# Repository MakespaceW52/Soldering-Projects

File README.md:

# Soldering Projects

\
Photo: © TINCON

Einfache Lötprojekte für den Einsatz in Bildungseinrichtungen und Makespaces.
Für alle Projekte stellen wir Gerber-Dateien zur Produktion über Platinenhersteller sowie KiCad-Projektdateien zur weiteren Bearbeitung bereit.

Easy soldering projects for educational purposes and makespaces.
For all projects, we provide Gerber files for production by PCB manufacturers, as well as KiCad project files for further modification and development.

Bei Fragen / for questions contact: makespace@tjfbg.de

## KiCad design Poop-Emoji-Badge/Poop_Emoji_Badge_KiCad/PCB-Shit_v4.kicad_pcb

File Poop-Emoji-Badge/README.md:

# Poop Emoji Badge

Easy PCB soldering project for educational purposes and makespaces.

Einfaches PCB-Lötprojekt für den Einsatz in Bildungseinrichtungen und Makespaces.

## Parts List

| Description                     | Quantity |
|---------------------------------|----------|
| RGB LEDs 5mm                    | 1        |
| Button (SMD)                    | 1        |
| CR2032 Battery Holder (SMD)     | 1        |
| CR2032 Battery                  | 1        |

You can find matching components on [blinkyparts.com](https://shop.blinkyparts.com/de/Einzelteile/).

Passende Bauteile gibt es bei [blinkyparts.com](https://shop.blinkyparts.com/de/Einzelteile/).

## Copyright and Authorship

Board: [CC-BY-SA 4.0](https://creativecommons.org/licenses/by-sa/4.0/) - Meko Mitte (tjfbg gGmbH)

Poop Emoji SVG: [CC-BY 4.0](https://creativecommons.org/licenses/by/4.0/) - [Codrops](https://www.svgrepo.com/svg/434338/shit-sunglasses)

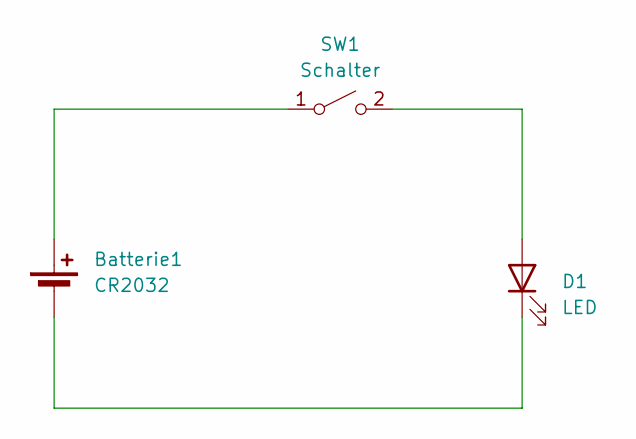
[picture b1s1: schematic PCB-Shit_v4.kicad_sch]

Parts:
Batterie1: CR2032; BatteryHolder_Keystone_1060_1x2032_HandSoldering
D1: LED; 5mm_SMD-Pad
SW1: Schalter; Push_Button

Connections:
unnamed: Batterie1.1 (+), SW1.1 (A)
unnamed: Batterie1.2 (-), D1.1 (K)
unnamed: D1.2 (A), SW1.2 (B)

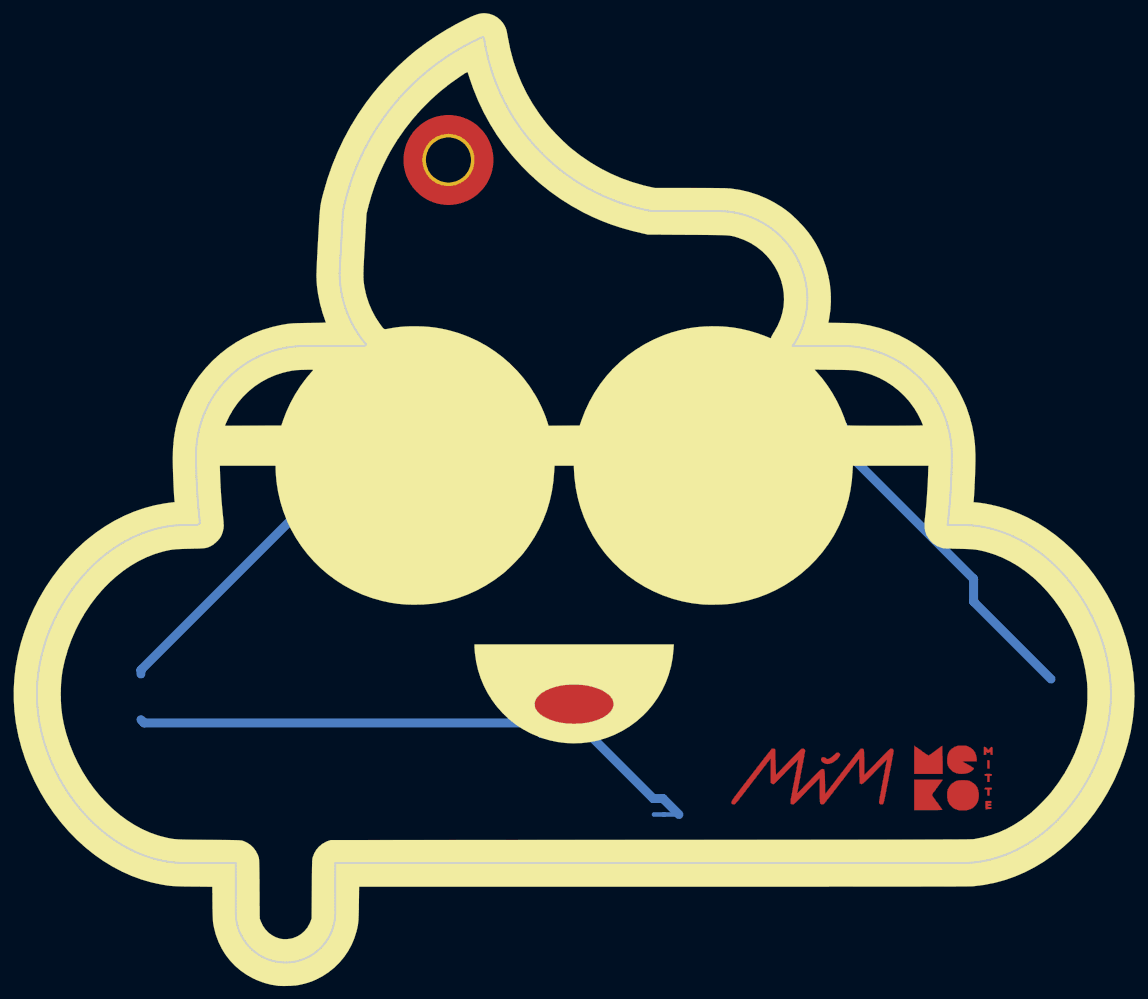
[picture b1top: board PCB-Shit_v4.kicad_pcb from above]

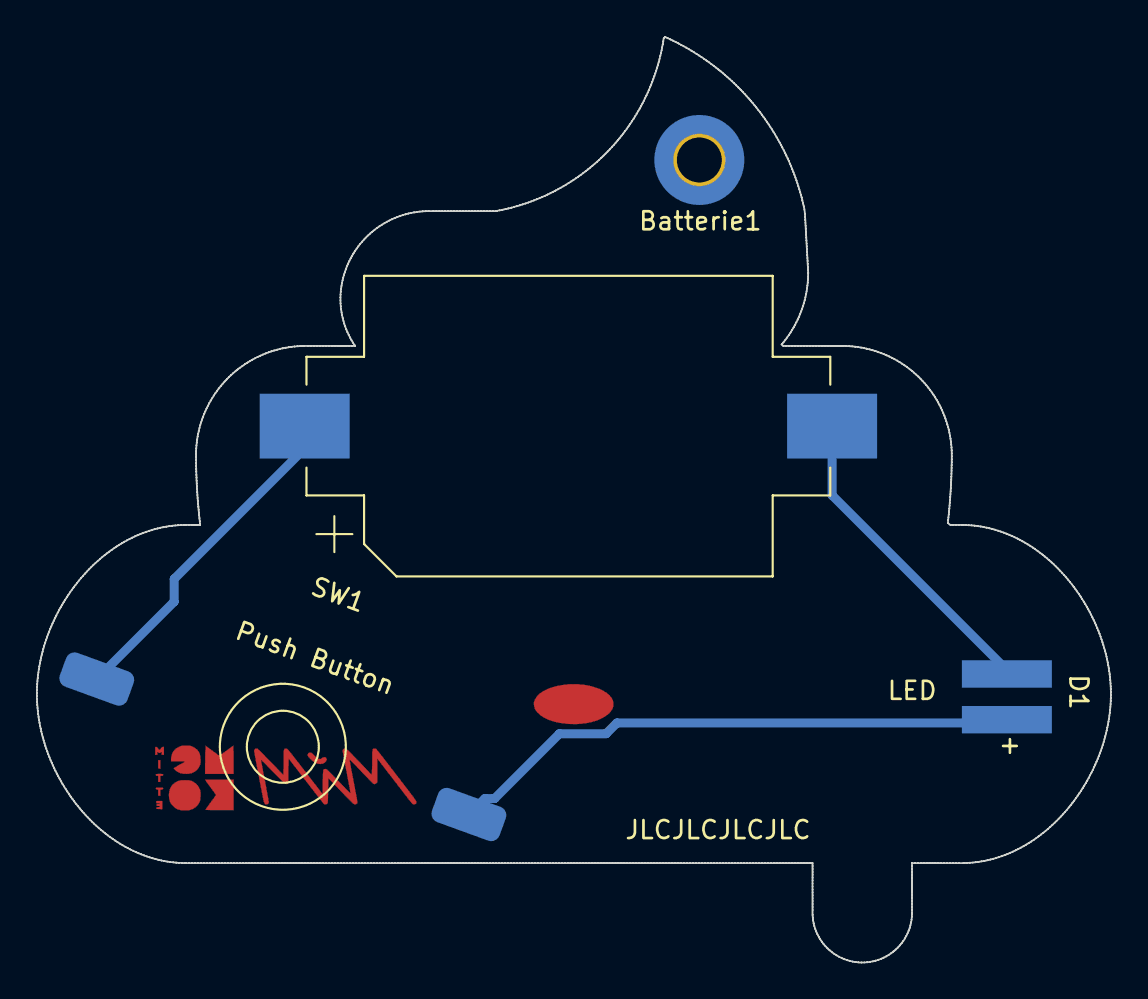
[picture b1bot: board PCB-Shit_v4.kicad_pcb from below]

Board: 2 copper layers, 59.7 x 51.4 mm, 4 parts (3 on the bottom side), 3 nets.

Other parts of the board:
Ref**: Val**; Meko_MIM_Logos

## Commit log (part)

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2026-02-23 Rename README to README.md
